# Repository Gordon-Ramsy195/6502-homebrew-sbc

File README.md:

# 6502 Homebrew SBC

**CPU**:w65c02
**RAM**:hm62256
**ROM**:28c256
**Clock**:1mhz
**Baud**:10416
**Uart to usb**:generic 6 pin

Included are schematics and pcb layout and gerbers from kicad. 
Possibly mistakes as ive only tested on a breadboard. 
Software and firmware shown works fine. 
AI was used in the creation of the image to ascii program as I never have or want to touch python and images together in my life. 
Have fun and break things with class and responsibility. 
Probably updates soon when I test a batch of pcbs.

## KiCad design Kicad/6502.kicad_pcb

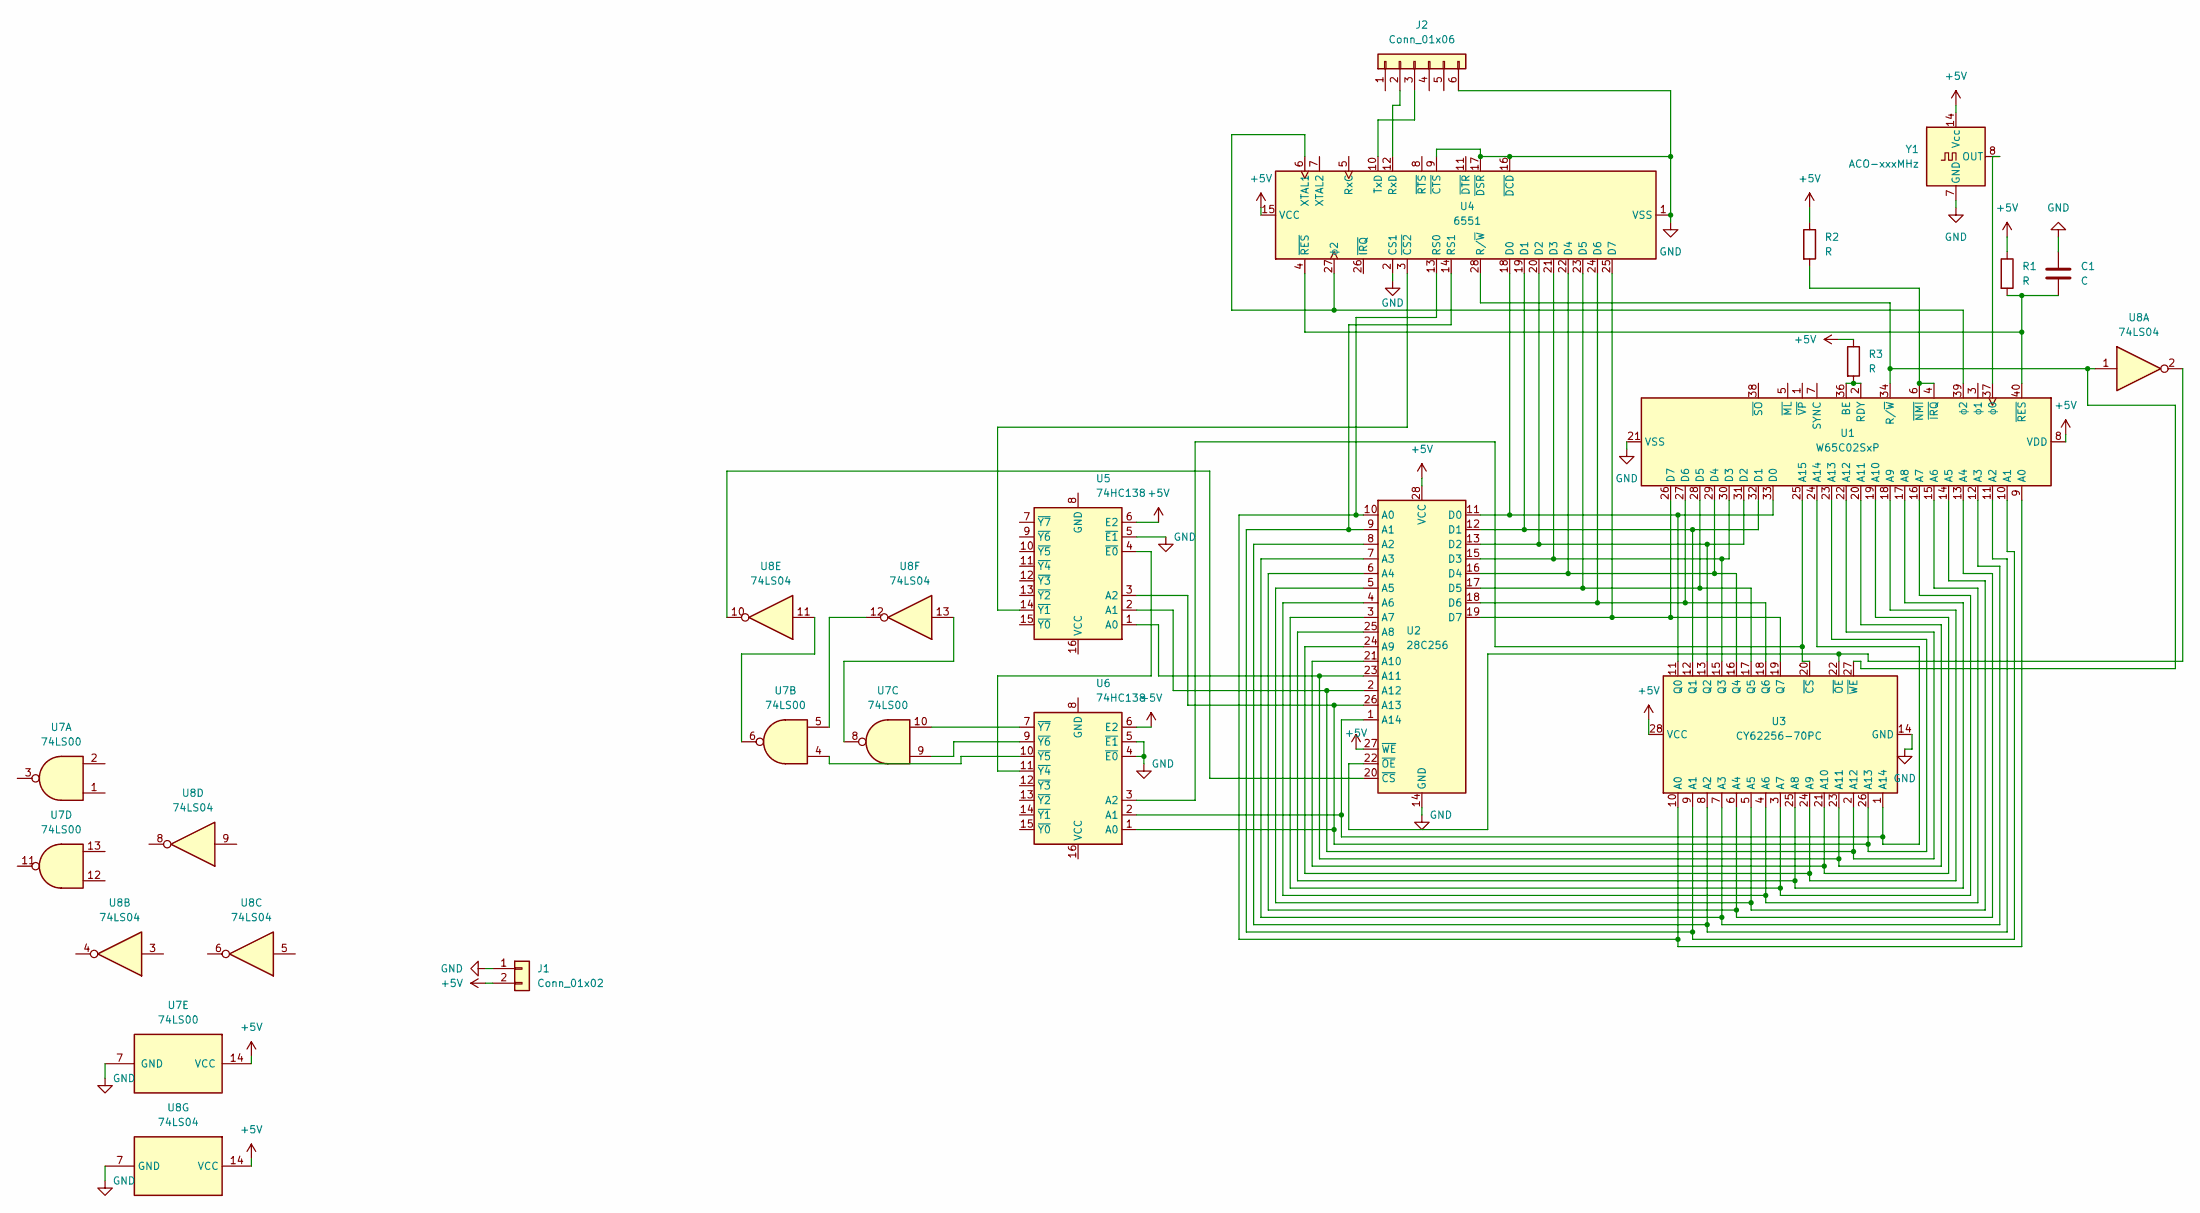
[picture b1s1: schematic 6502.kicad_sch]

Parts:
C1: C; C_Disc_D3.8mm_W2.6mm_P2.50mm
J1: Conn_01x02; 2_Holes_pwr
J2: Conn_01x06; 01x06_Headers
R1, R2, R3: R; R_Axial_DIN0207_L6.3mm_D2.5mm_P5.08mm_Vertical
U1: W65C02SxP; DIP-40_W15.24mm
U2: 28C256; DIP-28_W15.24mm
U3: CY62256-70PC; DIP-28_W15.24mm
U4: 6551; DIP-28_W15.24mm
U5, U6: 74HC138; DIP-16_W7.62mm
U7: 74LS00; DIP-14_W7.62mm
U8: 74LS04; DIP-14_W7.62mm
Y1: ACO-xxxMHz; Oscillator_DIP-14

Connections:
+5V: J1.2, R1.1, R2.1, R3.1, U1.8 (VDD), U2.27 (~WE), U2.28 (VCC), U3.28 (VCC), U4.15 (VCC), U5.6 (E2), U6.6 (E2), U7.14 (VCC), U8.14 (VCC), Y1.14 (Vcc)
GND: C1.1, J1.1, J2.6, U1.21 (VSS), U2.14 (GND), U3.14 (GND), U4.1 (VSS), U4.2 (CS1), U4.9 (~CTS), U4.16 (~DCD), U4.17 (~DSR), U5.5 (~E1), U6.4 (~E0), U6.5 (~E1), U7.7 (GND), U8.7 (GND), Y1.7 (GND)
unnamed: J2.2, U4.12 (RxD)
unnamed: J2.3, U4.10 (TxD)
unnamed: U1.9 (A0), U2.10 (A0), U3.10 (A0), U4.13 (RS0)
unnamed: U1.10 (A1), U2.9 (A1), U3.9 (A1), U4.14 (RS1)
unnamed: U1.11 (A2), U2.8 (A2), U3.8 (A2)
unnamed: U1.12 (A3), U2.7 (A3), U3.7 (A3)
unnamed: U1.13 (A4), U2.6 (A4), U3.6 (A4)
unnamed: U1.14 (A5), U2.5 (A5), U3.5 (A5)
unnamed: U1.15 (A6), U2.4 (A6), U3.4 (A6)
unnamed: U1.16 (A7), U2.3 (A7), U3.3 (A7)
unnamed: U1.17 (A8), U2.25 (A8), U3.25 (A8)
unnamed: U1.18 (A9), U2.24 (A9), U3.24 (A9)
unnamed: U1.19 (A10), U2.21 (A10), U3.21 (A10)
unnamed: U1.20 (A11), U2.23 (A11), U3.23 (A11), U5.1 (A0)
unnamed: U1.22 (A12), U2.2 (A12), U3.2 (A12), U5.2 (A1)
unnamed: U1.23 (A13), U2.26 (A13), U3.26 (A13), U5.3 (A2), U6.1 (A0)
unnamed: U1.24 (A14), U2.1 (A14), U3.1 (A14), U6.2 (A1)
unnamed: U1.25 (A15), U3.20 (~CS), U6.3 (A2)
unnamed: R3.2, U1.2 (RDY), U1.36 (BE)
unnamed: U1.33 (D0), U2.11 (D0), U3.11 (Q0), U4.18 (D0)
unnamed: U1.32 (D1), U2.12 (D1), U3.12 (Q1), U4.19 (D1)
unnamed: U1.31 (D2), U2.13 (D2), U3.13 (Q2), U4.20 (D2)
unnamed: U1.30 (D3), U2.15 (D3), U3.15 (Q3), U4.21 (D3)
unnamed: U1.29 (D4), U2.16 (D4), U3.16 (Q4), U4.22 (D4)
unnamed: U1.28 (D5), U2.17 (D5), U3.17 (Q5), U4.23 (D5)
unnamed: U1.27 (D6), U2.18 (D6), U3.18 (Q6), U4.24 (D6)
unnamed: U1.26 (D7), U2.19 (D7), U3.19 (Q7), U4.25 (D7)
unnamed: U1.34 (R/~W), U3.27 (~WE), U4.28 (R/~W), U8.1
unnamed: R2.2, U1.4 (~IRQ), U1.6 (~NMI)
unnamed: C1.2, R1.2, U1.40 (~RES), U4.4 (~RES)
unnamed: U1.37 (ϕ0), Y1.8 (OUT)
unnamed: U1.39 (ϕ2), U4.6 (XTAL1), U4.27 (ϕ2)
unnamed: U2.20 (~CS), U8.10
unnamed: U2.22 (~OE), U3.22 (~OE), U8.2
unnamed: U4.3 (~CS2), U5.14 (~Y1)
unnamed: U5.4 (~E0), U6.11 (~Y4)
unnamed: U6.10 (~Y5), U7.4
unnamed: U6.9 (~Y6), U7.9
unnamed: U6.7 (~Y7), U7.10
unnamed: U7.5, U8.12
unnamed: U7.6, U8.11
unnamed: U7.8, U8.13

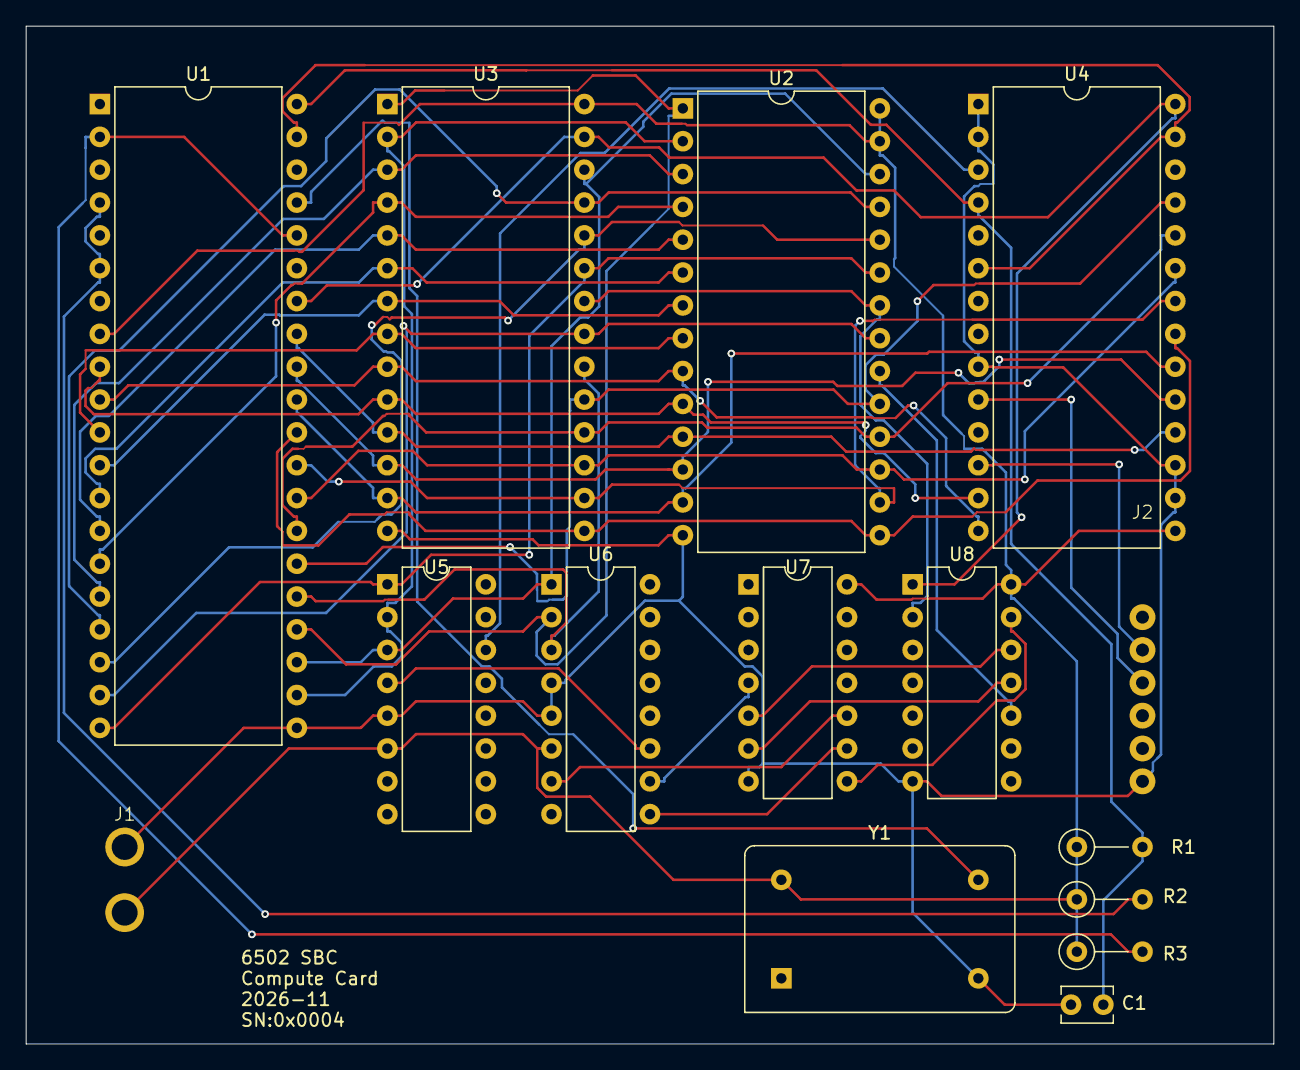
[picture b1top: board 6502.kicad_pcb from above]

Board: 2 copper layers, 96.5 x 78.7 mm, 15 parts (0 on the bottom side), 44 nets.
